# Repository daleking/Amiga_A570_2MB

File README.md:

# 2MB RAM Expansion for the A570 CD-ROM Drive

This is a simple 2MB RAM expansion as others have done for the A570.  It is
simply an implementation of the Commodore schematics.  People have done these
before but frustratingly I couldn't find any gerbers to make my own, hence this
implementation.

The PCB layout could be better - feel free to rework it.  But as it is, the
card is perfectly stable and works well.  I used 514400J 1Mx4 SOJ DRAM chips
which are easy to find.  Interestingly 424400 chips don't work (at least the
ones I tried) giving a black / blinking screen, so better to stick with what
CBM specified on the schematics.

For the lazy, you can order gerbers from
[DirtyPCBs](http://dirtypcbs.com/store/designer/details/dalek/6305/2mb-ram-expansion-for-the-amiga-a570-cd-rom-drive)
or from your own board house (see the releases page), or remix how you like
with KiCAD.

If you scrounge old single sided 4MB or dual sided 8MB 72-pin PC SIMMs you will
probably find some suitable DRAM.

You will also need a 2x20pin female right angle header, and some decoupling
caps.  The schematics say 0.33uF but I used 0.1uF with no issues and it even
works if you leave the caps off.

The jumper is the RAM enable jumper.  Connect it to a wired external switch if
you really feel you want to be able to disable the RAM without opening the
cover again.

## Schematic

## Front

## Bottom

## Connected

## Memory Test

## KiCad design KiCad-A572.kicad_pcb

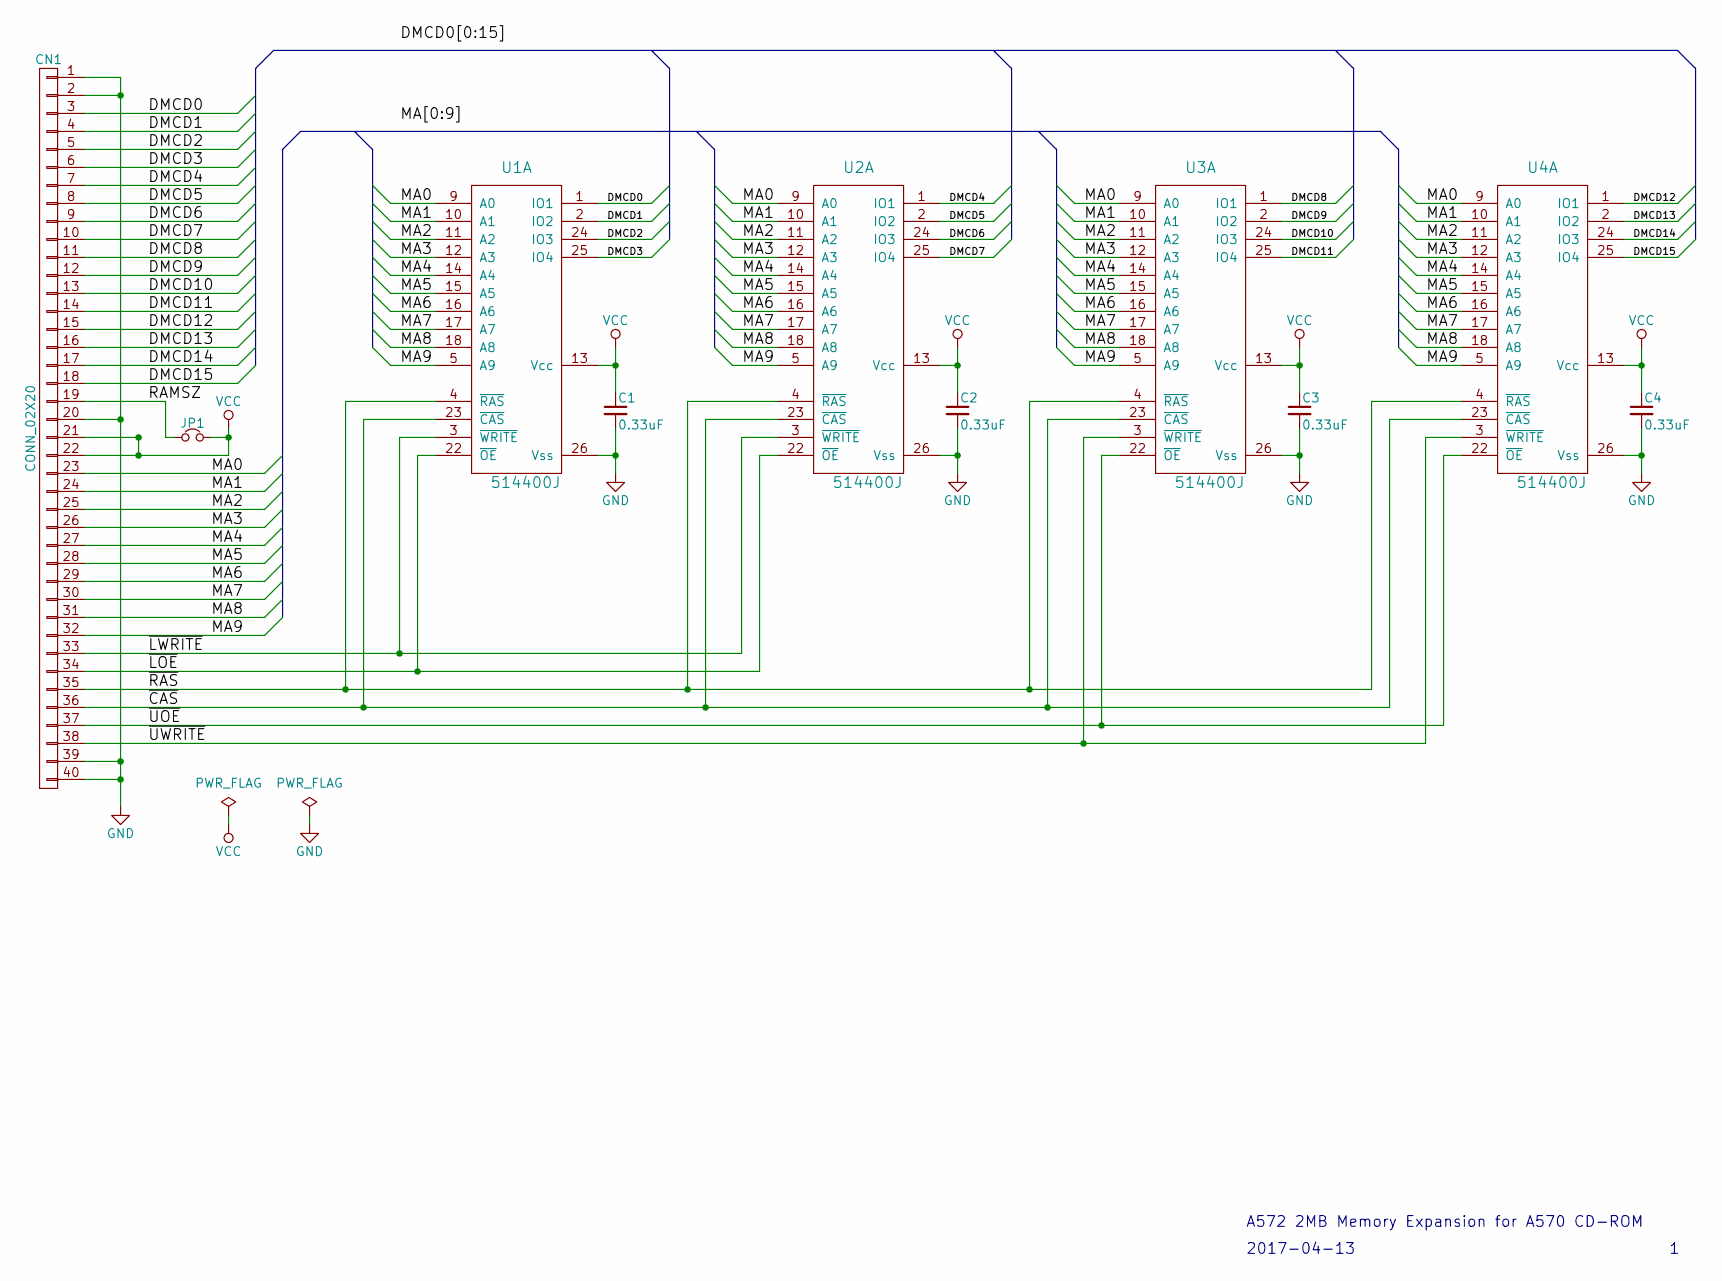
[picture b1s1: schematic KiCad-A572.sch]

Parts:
C1, C2, C3, C4: 0.33uF; C_0603_HandSoldering
CN1: CONN_02X20; Socket_Strip_Angled_2x20_Pitch2.54mm
JP1: Jumper_NC_Small; Pin_Header_Angled_1x02_Pitch2.54mm
U1, U2, U3, U4: 514400J; SOJ-20-26

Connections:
/DMCD0: CN1.3, U1.1 (IO1)
/DMCD1: CN1.4, U1.2 (IO2)
/DMCD2: CN1.5, U1.24 (IO3)
/DMCD3: CN1.6, U1.25 (IO4)
/DMCD4: CN1.7, U2.1 (IO1)
/DMCD5: CN1.8, U2.2 (IO2)
/DMCD6: CN1.9, U2.24 (IO3)
/DMCD7: CN1.10, U2.25 (IO4)
/DMCD8: CN1.11, U3.1 (IO1)
/DMCD9: CN1.12, U3.2 (IO2)
/DMCD10: CN1.13, U3.24 (IO3)
/DMCD11: CN1.14, U3.25 (IO4)
/DMCD12: CN1.15, U4.1 (IO1)
/DMCD13: CN1.16, U4.2 (IO2)
/DMCD14: CN1.17, U4.24 (IO3)
/DMCD15: CN1.18, U4.25 (IO4)
/MA0: CN1.23, U1.9 (A0), U2.9 (A0), U3.9 (A0), U4.9 (A0)
/MA1: CN1.24, U1.10 (A1), U2.10 (A1), U3.10 (A1), U4.10 (A1)
/MA2: CN1.25, U1.11 (A2), U2.11 (A2), U3.11 (A2), U4.11 (A2)
/MA3: CN1.26, U1.12 (A3), U2.12 (A3), U3.12 (A3), U4.12 (A3)
/MA4: CN1.27, U1.14 (A4), U2.14 (A4), U3.14 (A4), U4.14 (A4)
/MA5: CN1.28, U1.15 (A5), U2.15 (A5), U3.15 (A5), U4.15 (A5)
/MA6: CN1.29, U1.16 (A6), U2.16 (A6), U3.16 (A6), U4.16 (A6)
/MA7: CN1.30, U1.17 (A7), U2.17 (A7), U3.17 (A7), U4.17 (A7)
/MA8: CN1.31, U1.18 (A8), U2.18 (A8), U3.18 (A8), U4.18 (A8)
/MA9: CN1.32, U1.5 (A9), U2.5 (A9), U3.5 (A9), U4.5 (A9)
/RAMSZ: CN1.19, JP1.1
/~CAS: CN1.36, U1.23 (~CAS), U2.23 (~CAS), U3.23 (~CAS), U4.23 (~CAS)
/~LOE: CN1.34, U1.22 (~OE), U2.22 (~OE)
/~LWRITE: CN1.33, U1.3 (~WRITE), U2.3 (~WRITE)
/~RAS: CN1.35, U1.4 (~RAS), U2.4 (~RAS), U3.4 (~RAS), U4.4 (~RAS)
/~UOE: CN1.37, U3.22 (~OE), U4.22 (~OE)
/~UWRITE: CN1.38, U3.3 (~WRITE), U4.3 (~WRITE)
GND: C1.2, C2.2, C3.2, C4.2, CN1.1, CN1.2, CN1.20, CN1.39, CN1.40, U1.26 (Vss), U2.26 (Vss), U3.26 (Vss), U4.26 (Vss)
VCC: C1.1, C2.1, C3.1, C4.1, CN1.21, CN1.22, JP1.2, U1.13 (Vcc), U2.13 (Vcc), U3.13 (Vcc), U4.13 (Vcc)

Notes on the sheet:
A572 2MB Memory Expansion for A570 CD-ROM
2017-04-13

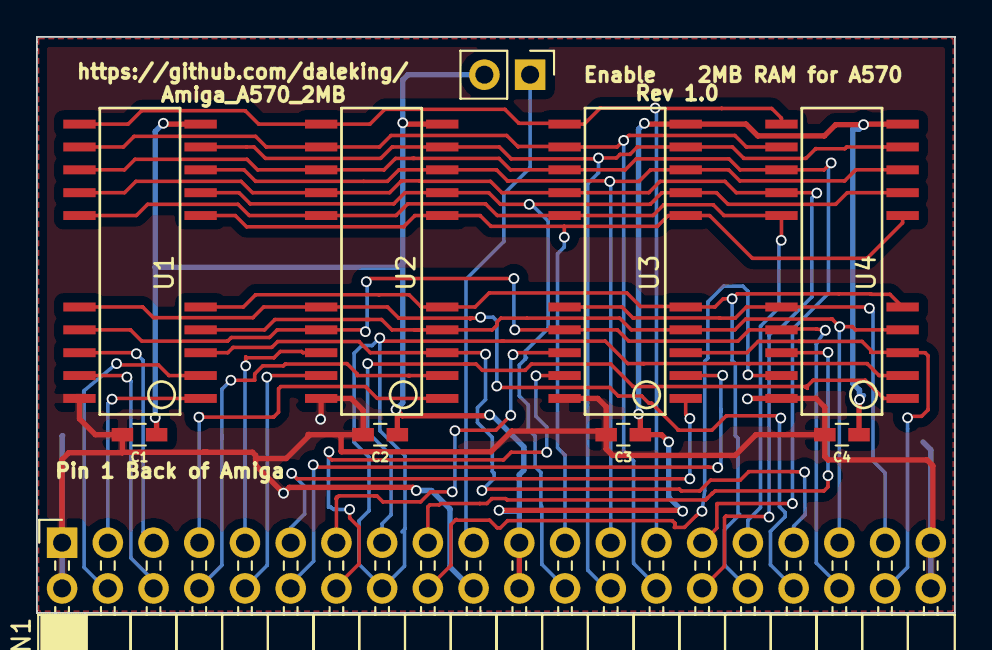
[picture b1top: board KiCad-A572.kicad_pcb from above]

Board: 2 copper layers, 51.0 x 32.0 mm, 10 parts (0 on the bottom side), 35 nets.

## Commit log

2019-05-14 upload
2019-05-14 gerbers
